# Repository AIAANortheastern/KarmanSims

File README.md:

# KarmanSims
Project Karman's simulations

Design ins

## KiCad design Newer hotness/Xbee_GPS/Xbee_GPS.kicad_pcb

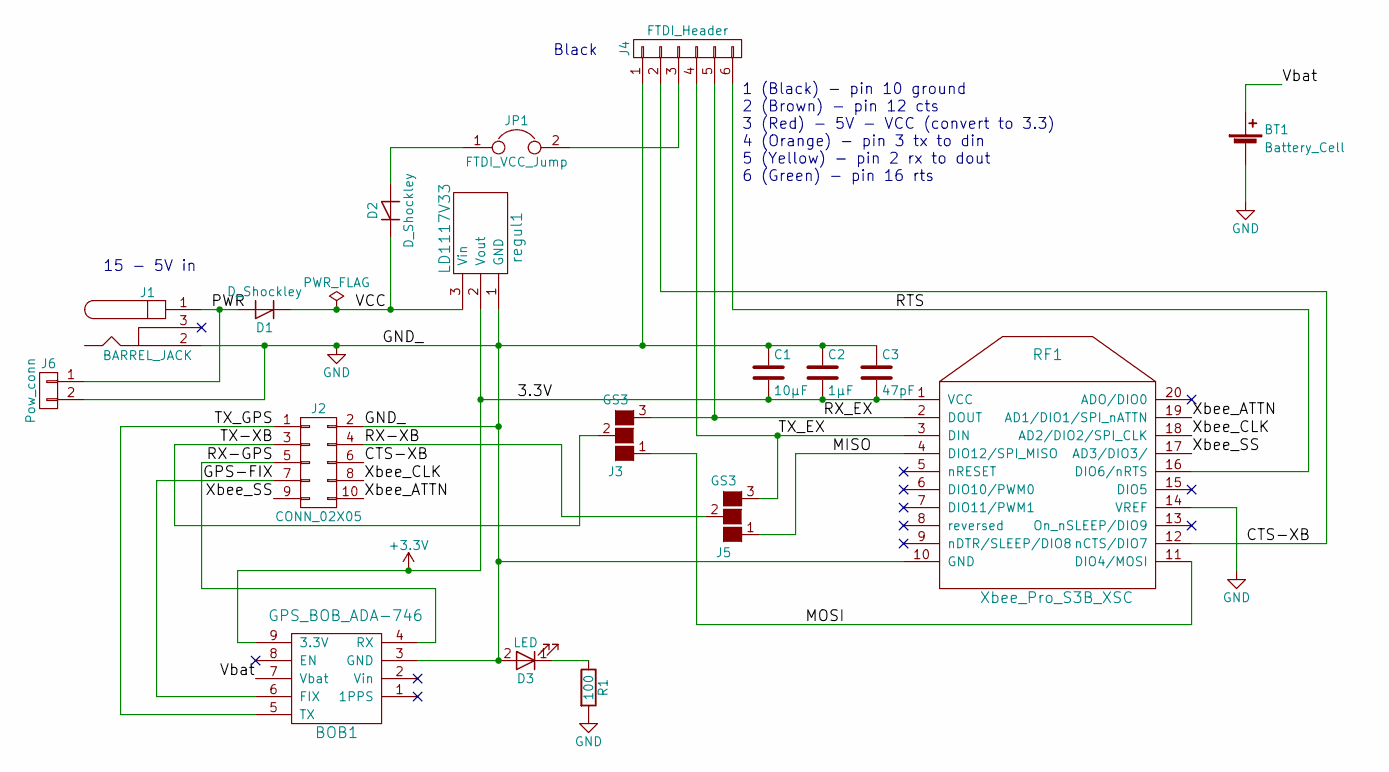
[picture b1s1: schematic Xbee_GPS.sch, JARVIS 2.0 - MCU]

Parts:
BOB1: GPS_BOB_ADA-746; GPS_BOB_A746
BT1: Battery_Cell; CR1220_Conn_TH_MPD
C1: 10µF; C_Rect_L4.6mm_W2.0mm_P2.50mm_MKS02_FKP02
C2: 1µF; C_Rect_L4.6mm_W2.0mm_P2.50mm_MKS02_FKP02
C3: 47pF; C_Rect_L4.6mm_W2.0mm_P2.50mm_MKS02_FKP02
D1, D2: D_Shockley; D_DO-35_SOD27_P7.62mm_Horizontal
D3: LED; LED-3MM
J1: BARREL_JACK; BARREL_JACK_W_Header_Holes
J2: CONN_02X05; IDC_Header_Straight_10pins
J3, J5: GS3
J4: FTDI_Header; Pin_Header_Straight_1x06_Pitch2.54mm
J6: Pow_conn; Pin_Header_Straight_1x02
JP1: FTDI_VCC_Jump; Pin_Header_Straight_1x02_Pitch2.54mm
R1: 100; R_Axial_DIN0207_L6.3mm_D2.5mm_P7.62mm_Horizontal
RF1: Xbee_Pro_S3B_XSC; Xbee_Pro_S3B
regul1: LD1117V33; TO-220_Neutral123_Vertical

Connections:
+3V3: BOB1.9 (3.3V), C1.2, C2.2, C3.2, RF1.1 (VCC), regul1.2 (Vout)
/CTS-XB: J2.6, J4.2, RF1.12 (nCTS/DIO7)
/GPS-FIX: BOB1.6 (FIX), J2.7
/MISO: J5.1 (G1), RF1.4 (DIO12/SPI_MISO)
/MOSI: J3.1 (G1), RF1.11 (DIO4/MOSI)
/PWR: D1.2 (A), J1.1, J6.1
/RTS: J4.6, RF1.16 (DIO6/nRTS)
/RX-GPS: BOB1.4 (RX), J2.5
/RX-XB: J2.4, J5.2 (G2)
/RX_EX: J3.3 (G3), J4.5, RF1.2 (DOUT)
/TX-XB: J2.3, J3.2 (G2)
/TX_EX: J4.4, J5.3 (G3), RF1.3 (DIN)
/TX_GPS: BOB1.5 (TX), J2.1
/VCC: D1.1 (K), D2.1 (K), regul1.3 (Vin)
/Vbat: BOB1.7 (Vbat), BT1.1 (+)
/Xbee_ATTN: J2.10, RF1.19 (AD1/DIO1/SPI_nATTN)
/Xbee_CLK: J2.8, RF1.18 (AD2/DIO2/SPI_CLK)
/Xbee_SS: J2.9, RF1.17 (AD3/DIO3/)
GND: BOB1.3 (GND), BT1.2 (-), C1.1, C2.1, C3.1, D3.2 (A), J1.2, J2.2, J4.1, J6.2, R1.2, RF1.10 (GND), RF1.14 (VREF), regul1.1 (GND)
unnamed: D2.2 (A), JP1.1
unnamed: D3.1 (K), R1.1
unnamed: J4.3, JP1.2

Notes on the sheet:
Black
1 (Black) - pin 10 ground 2 (Brown) - pin 12 cts 3 (Red) - 5V - VCC (convert to 3.3) 4 (Orange) - pin 3 tx to din 5 (Yellow) - pin 2 rx to dout 6 (Green) - pin 16 rts
15 - 5V in

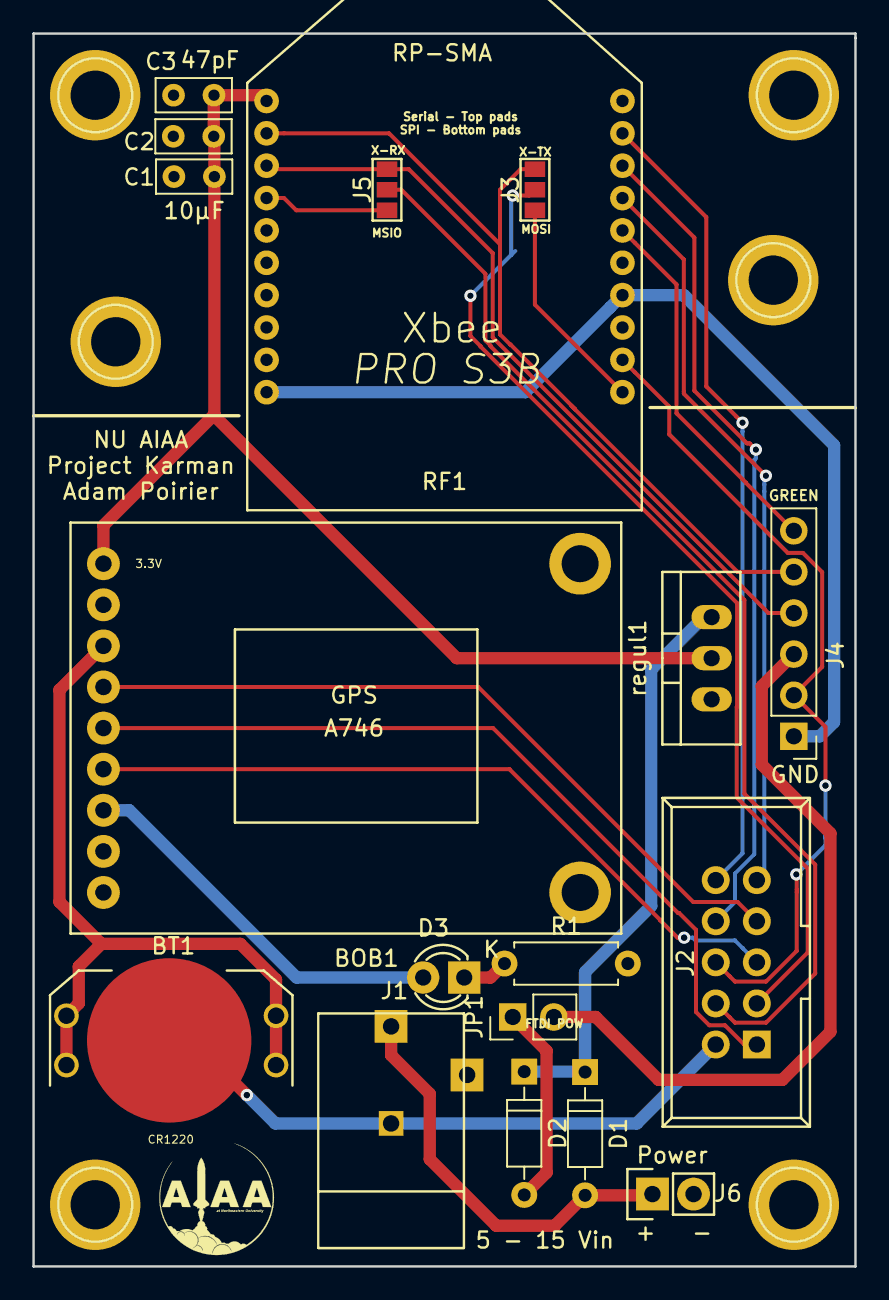
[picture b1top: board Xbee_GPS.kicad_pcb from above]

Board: 2 copper layers, 50.8 x 76.2 mm, 18 parts (0 on the bottom side), 22 nets.

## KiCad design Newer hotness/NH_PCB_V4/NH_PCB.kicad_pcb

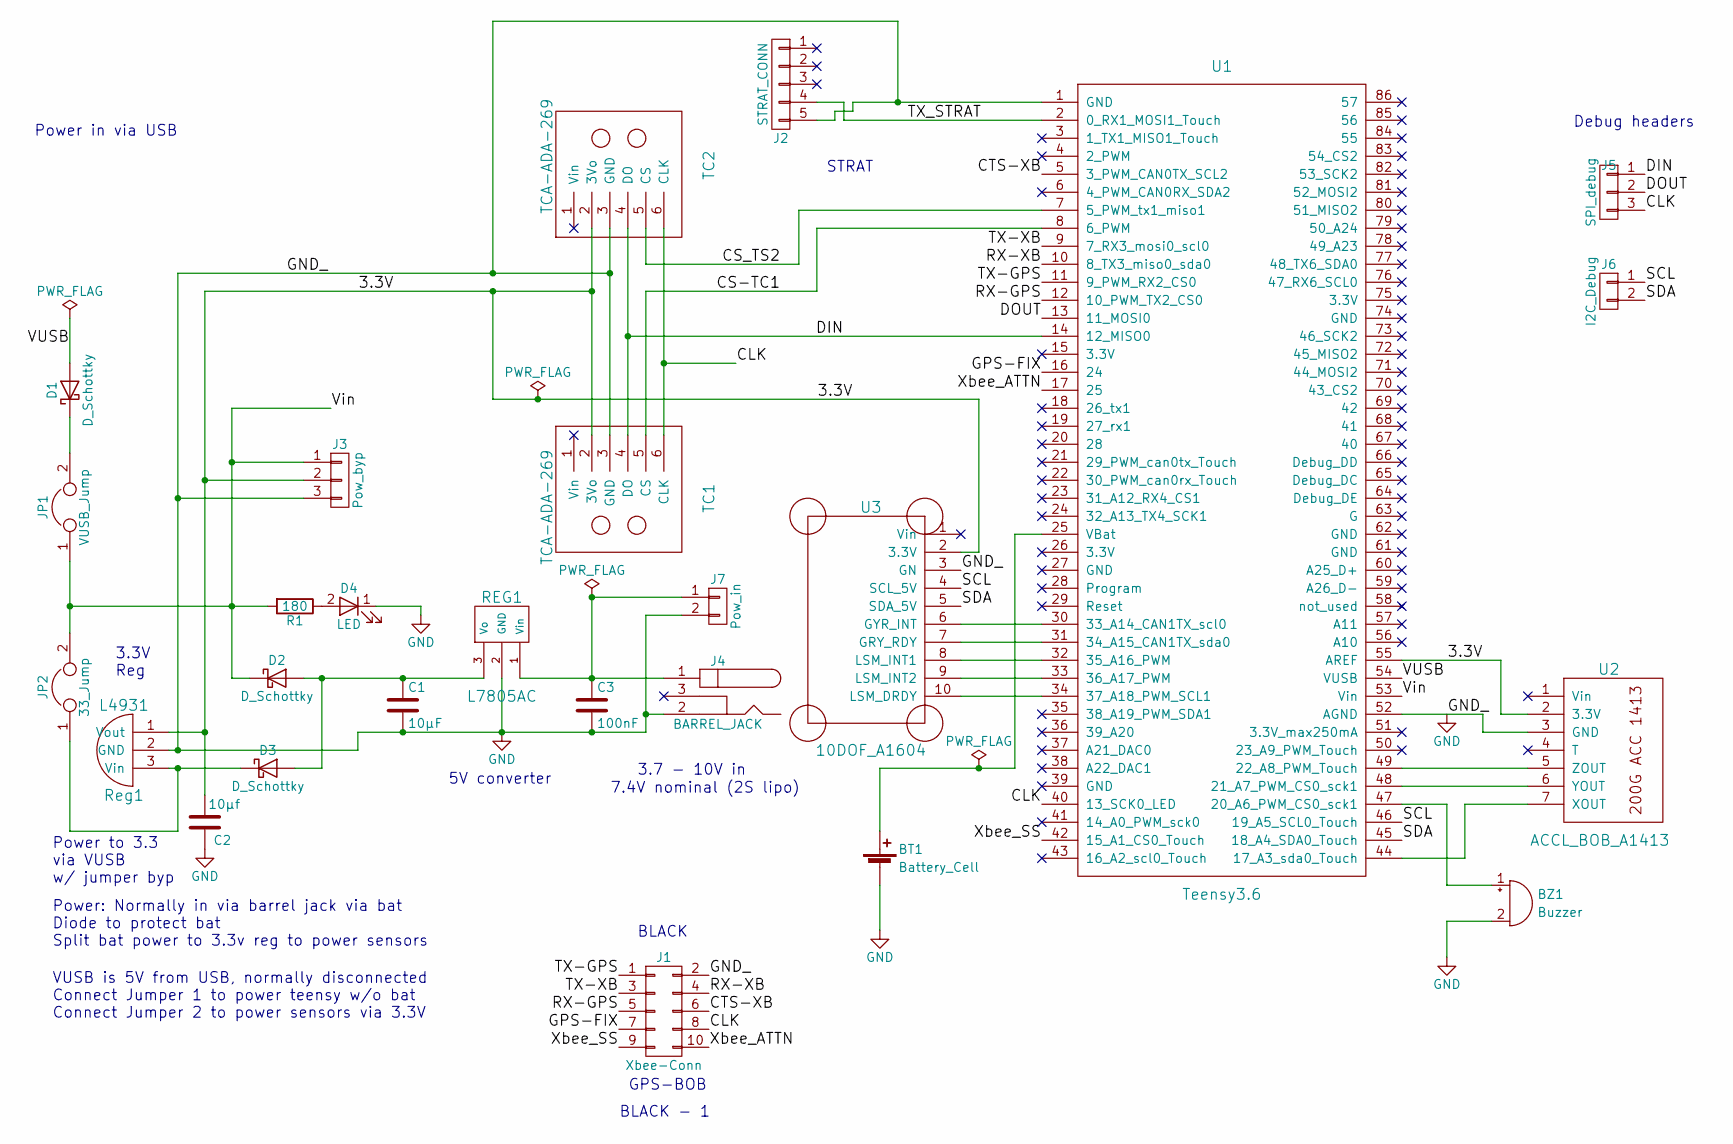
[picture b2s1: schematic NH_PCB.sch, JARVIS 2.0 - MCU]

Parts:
BT1: Battery_Cell; CR1220_Conn_TH_MPD
BZ1: Buzzer; Buzzer_A1536
C1: 10µF; C_Rect_L4.6mm_W2.0mm_P2.50mm_MKS02_FKP02
C2: 10µf; C_Rect_L4.6mm_W2.0mm_P2.50mm_MKS02_FKP02
C3: 100nF; C_Rect_L4.6mm_W2.0mm_P2.50mm_MKS02_FKP02
D1, D2, D3: D_Schottky; Diode_DO-41_SOD81_Vertical_AnodeUp
D4: LED; LED-3MM
J1: Xbee-Conn; IDC_Header_Straight_10pins
J2: STRAT_CONN; JST_SH_SM05B-SRSS-TB_05x1.00mm_Angled
J3: Pow_byp; Pin_Header_Straight_1x03
J4: BARREL_JACK; BARREL_JACK_W_Header_Holes
J5: SPI_debug; Pin_Header_Straight_1x03_Pitch2.54mm
J6: I2C_Debug; Pin_Header_Straight_1x02_Pitch2.54mm
J7: Pow_in; Pin_Header_Straight_1x02
JP1: VUSB_Jump; Pin_Header_Straight_1x02_Pitch2.54mm
JP2: 33_Jump; Pin_Header_Straight_1x02_Pitch2.54mm
R1: 180; R_Axial_DIN0207_L6.3mm_D2.5mm_P10.16mm_Horizontal
REG1: L7805AC; TO-220_Vertical
Reg1: L4931; TO-92_Inline_Wide
TC1, TC2: TCA-ADA-269; TCA_BOB_ADA269
U1: Teensy3.6; Teensy35_36
U2: ACCL_BOB_A1413; Accel_BOB_A1413
U3: 10DOF_A1604; 10DOF_BOB_ADA16014

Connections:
/3.3V: C2.2, J3.2, Reg1.1 (Vout), TC1.2 (3Vo), TC2.2 (3Vo), U1.55 (AREF), U2.2 (3.3V), U3.2 (3.3V)
/CLK: J1.8, J5.3, TC1.6 (CLK), TC2.6 (CLK), U1.40 (13_SCK0_LED)
/CS-TC1: TC1.5 (CS), U1.8 (6_PWM)
/CS_TS2: TC2.5 (CS), U1.7 (5_PWM_tx1_miso1)
/CTS-XB: J1.6, U1.5 (3_PWM_CAN0TX_SCL2)
/DIN: J5.1, TC1.4 (DO), TC2.4 (DO), U1.14 (12_MISO0)
/DOUT: J5.2, U1.13 (11_MOSI0)
/GPS-FIX: J1.7, U1.16 (24)
/RX-GPS: J1.5, U1.12 (10_PWM_TX2_CS0)
/RX-XB: J1.4, U1.10 (8_TX3_miso0_sda0)
/SCL: J6.1, U1.46 (19_A5_SCL0_Touch), U3.4 (SCL_5V)
/SDA: J6.2, U1.45 (18_A4_SDA0_Touch), U3.5 (SDA_5V)
/TX-GPS: J1.1, U1.11 (9_PWM_RX2_CS0)
/TX-XB: J1.3, U1.9 (7_RX3_mosi0_scl0)
/TX_STRAT: J2.4, U1.2 (0_RX1_MOSI1_Touch)
/VUSB: D1.2 (A), U1.54 (VUSB)
/Vin: D2.1 (K), J3.1, JP1.1, JP2.2, R1.2, U1.53 (Vin)
/Xbee_ATTN: J1.10, U1.17 (25)
/Xbee_SS: J1.9, U1.42 (15_A1_CS0_Touch)
GND: BT1.2 (-), BZ1.2 (+), C1.2, C2.1, C3.2, D4.1 (K), J1.2, J2.5, J3.3, J4.2, J7.2, REG1.2 (GND), Reg1.2 (GND), TC1.3 (GND), TC2.3 (GND), U1.1 (GND), U1.52 (AGND), U2.3 (GND), U3.3 (GN)
unnamed: BT1.1 (+), U1.25 (VBat)
unnamed: BZ1.1 (-), U1.47 (20_A6_PWM_CS0_sck1)
unnamed: C1.1, D2.2 (A), D3.2 (A), REG1.3 (Vo)
unnamed: C3.1, J4.1, J7.1, REG1.1 (Vin)
unnamed: D1.1 (K), JP1.2
unnamed: D3.1 (K), JP2.1, Reg1.3 (Vin)
unnamed: D4.2 (A), R1.1
unnamed: U1.30 (33_A14_CAN1TX_scl0), U3.6 (GYR_INT)
unnamed: U1.31 (34_A15_CAN1TX_sda0), U3.7 (GRY_RDY)
unnamed: U1.32 (35_A16_PWM), U3.8 (LSM_INT1)
unnamed: U1.33 (36_A17_PWM), U3.9 (LSM_INT2)
unnamed: U1.34 (37_A18_PWM_SCL1), U3.10 (LSM_DRDY)
unnamed: U1.44 (17_A3_sda0_Touch), U2.7 (XOUT)
unnamed: U1.48 (21_A7_PWM_CS0_sck1), U2.6 (YOUT)
unnamed: U1.49 (22_A8_PWM_Touch), U2.5 (ZOUT)

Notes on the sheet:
BLACK - 1
GPS-BOB
BLACK
STRAT
Debug headers
3.7 - 10V in
Power in via USB
7.4V nominal (2S lipo)
3.3V Reg
Power to 3.3 via VUSB w/ jumper byp
Power: Normally in via barrel jack via bat Diode to protect bat Split bat power to 3.3v reg to power sensors
VUSB is 5V from USB, normally disconnected Connect Jumper 1 to power teensy w/o bat Connect Jumper 2 to power sensors via 3.3V
5V converter

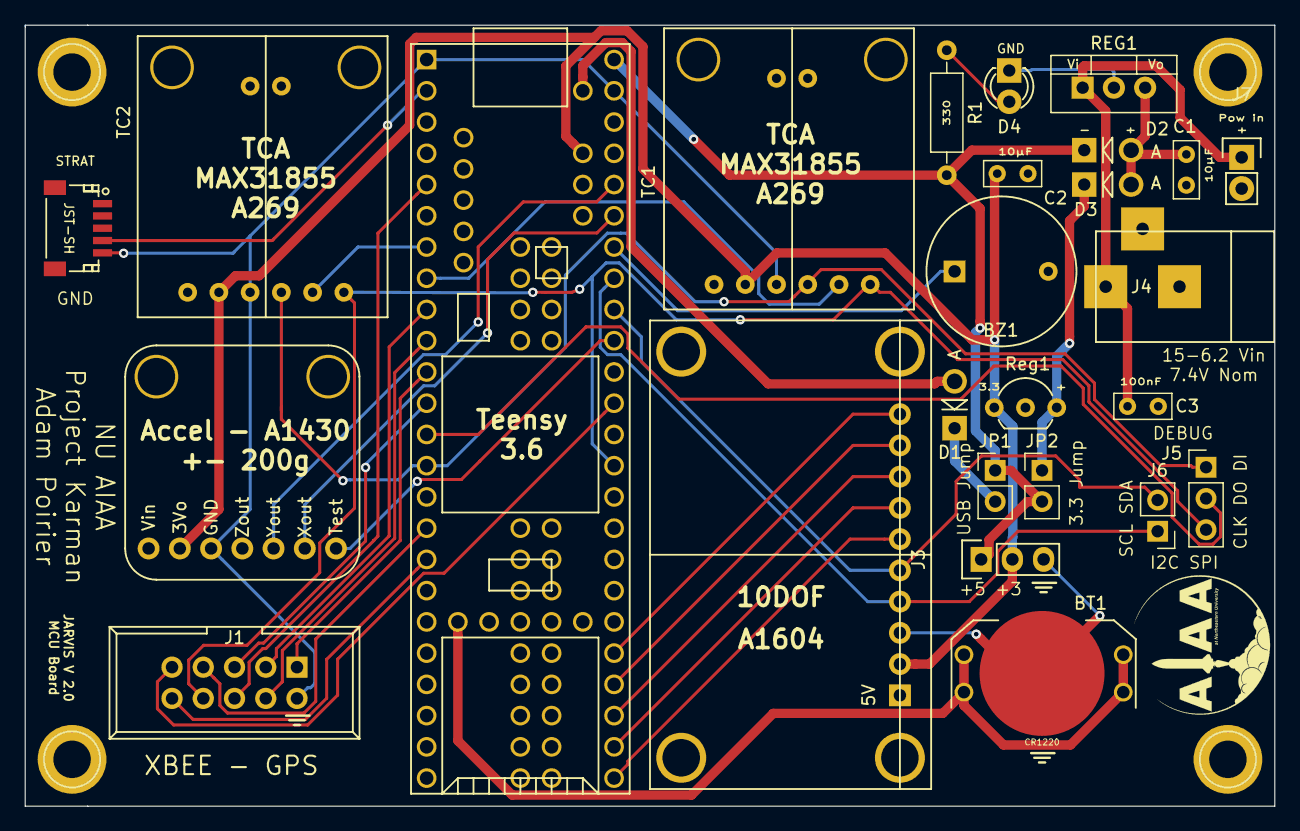
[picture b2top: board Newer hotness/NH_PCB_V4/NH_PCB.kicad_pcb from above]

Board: 2 copper layers, 101.6 x 63.5 mm, 26 parts (0 on the bottom side), 35 nets.

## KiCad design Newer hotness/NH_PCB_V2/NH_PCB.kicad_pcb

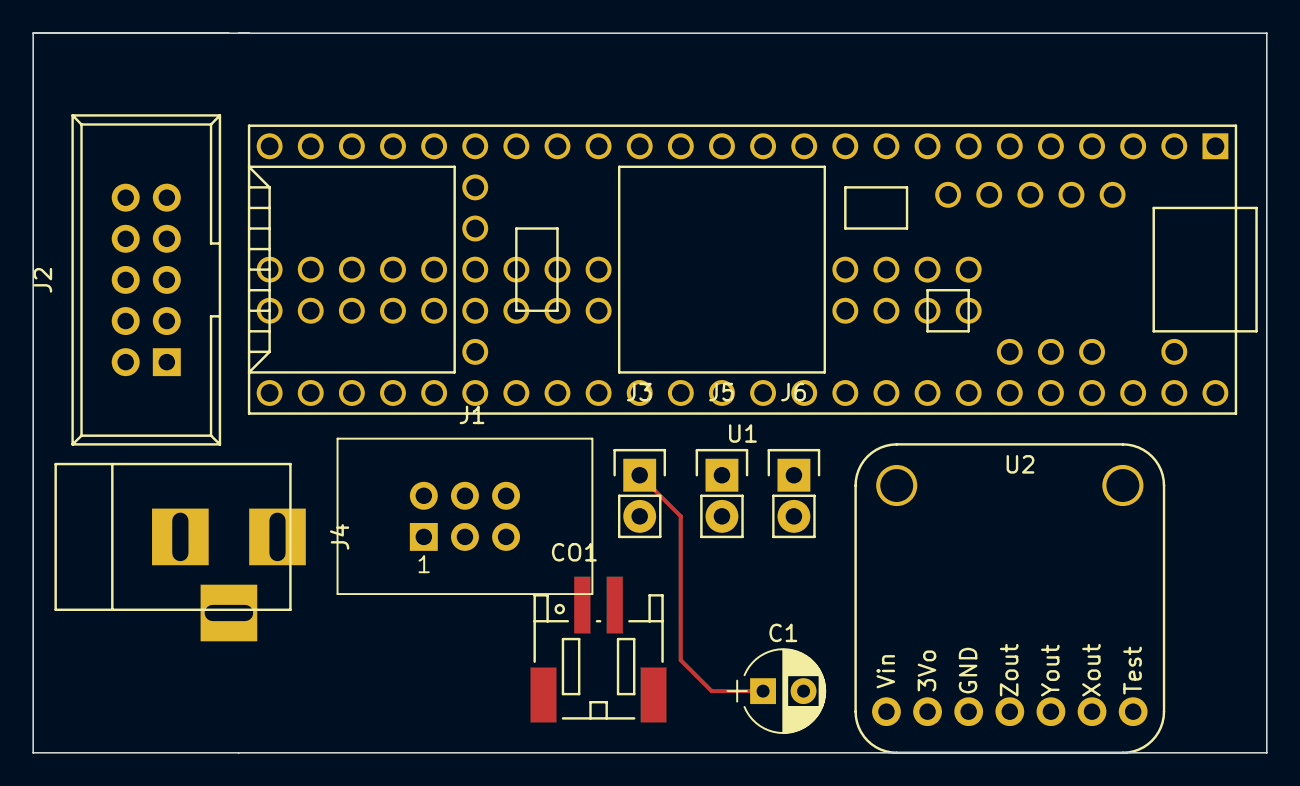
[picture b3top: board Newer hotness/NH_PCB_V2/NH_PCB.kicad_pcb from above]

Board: 2 copper layers, 76.2 x 44.4 mm, 10 parts (0 on the bottom side), 18 nets.

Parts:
C1: .1µf; CP_Radial_D5.0mm_P2.50mm
CO1: CONN_JST_2Pin; JST_PH_S2B-PH-SM4-TB_02x2.00mm_Angled
J1: CONN_02X03; IDC_Header_Straight_6pins
J2: CONN_02X05; IDC_Header_Straight_10pins
J3: POW_BYP; Pin_Header_Straight_1x02
J4: BARREL_JACK
J5, J6: CONN_01X02; Pin_Header_Straight_1x02
U1: Teensy3.5; Teensy35_36
U2: ACCL_BOB_A1413; Accel_BOB_A1413

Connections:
/5V: C1.1, J3.1, J4.1, U1.53, U1.55, U2.1
/CLK: J2.1, U1.40
/CS-TC1: J2.2, U1.8
/CTS-XB: J1.6, U1.5
/DIN: J2.3, J5.1, U1.13
/DOUT: J5.2, U1.14
/GIN: J2.7, U1.30
/GIND: J2.8, U1.31
/GND_: C1.2, J1.2, J2.4, J3.2, J4.2, U1.1, U1.52, U2.3
/RX-GPS: J1.5, U1.12
/RX-XB: J1.4, U1.10
/SCL: J2.5, J6.1, U1.46
/SDA: J2.6, J6.2, U1.45
/TX-XB: J1.3, U1.9
/XTRA: J2.10, U1.32
unnamed: U1.44, U2.7
unnamed: U1.48, U2.6
unnamed: U1.49, U2.5

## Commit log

2016-06-09 Test upload
2016-06-10 sync with drive
    added simulations in ~/Project Karman/Research/Designs/Simulations from
    Google Drive
    should really change the filenames to things that are borderline
    meaningful whatsoever
2016-06-13 Uploaded v1 RAS aero sims, along with updated open rocket files
2016-06-14 updated sims
2016-06-16 updated sims with correct mass balance
2016-06-16 I made a text file because adam said so
2016-06-21 Updated motor files
2016-06-21 added flight simulation results
2016-07-06 added legacy sims
2016-07-06 updated organisation structure
2016-07-13 updated files
2016-07-25 Updated NH sim
2016-08-15 Added parachute test rocket file
2016-08-15 Updated p-test cal
2016-10-15 Add files via upload
    Updated motor section to match the one we have
2016-10-15 Updated motor section
    Changed motor section dimensions to match the one we have
2016-10-17 Updated BTB file to properly stage
2016-10-17 added v2 of final upper stage
2016-10-18 updated to proper sizes
2016-10-19 Added actual length of upper body tube
2016-10-19 Fixing the commits
2016-10-21 Fixed location of airtight bulkhead
2016-10-22 Added the updated parachute test rocket
2016-11-09 added some files
2016-11-11 Changed motor
    Brought apogee down to about 3000 ft
2016-11-21 making sure I'm up to date
2016-12-07 Testing github on Simulations Computer
2016-12-09 Added Parachute test V4 sim
2016-12-18 making sure up to date
2016-12-18 Updated PTR V3, CAUTION: THIS FILE MAY BE OUT OF DATE BECAUSE OF PROBLEMS ON MY COMPUTER. If you know you have the most recent version, copy the file before you pull changes, then override with your 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
2017-01-02 Updated PRT sim to reflect accurate fin location. MASS OF PARACHUTE NEEDS TO BE UPDATED
2017-01-06 Updated PTR file to have 100% accurate e-bay length. NOTE: Mass of ebay is not final, and parachute and recovery harnesses are NOT massed correctly. Additionally moved fins up to comply with final de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
2017-02-17 adding PTR_V4
2017-02-18 added new full scale simulation (kevlar wraped CF)
2017-02-19 added current motor file for P
2017-02-19 added updated RASaero full scale sim
2017-02-19 Rename rasp-2:19:17.eng to rasp-2-19-17.eng
2017-02-21 Updated Parachute test to current specifications: Parachute Test V3.5.1.ork
2017-02-22 Updated BTB
2017-02-24 Updated BTB sim and added RASAero simulation
2017-02-28 updated PTR and BTB sim, along with BTB RASAero model
2017-03-01 updated BTB and PTR to use motors we are buying
2017-03-09 added standard atmospheres for reference
2017-03-12 added flight data folder with recorded PTR flight data exports
2017-03-13 updated stuff
2017-03-14 updated BTB sustainer
2017-03-14 Updated BTB RASAero
2017-03-19 updated BTB sim with 4G motor
2017-03-21 making sure sim computer is up to date
2017-03-21 removed legacy BTB sim
2017-03-30 added go-pro assembly
2017-03-30 Added the go pro assmb.
2017-04-01 updated BTB / infinity & beyond sim to work with L1115
2017-05-04 changed fin LE/TE to .5 in
2017-05-27 added motor info
2017-06-01 Added new aluminum sim
2017-07-09 Added PCB designs
2017-07-12 added final newer hotness boards
2017-07-19 PTR updates for new av-bay
2017-07-23 updated v4 pcb
2017-07-26 telemetry PCB updates
2017-07-28 updated PCB files
2017-07-31 finalized PCB layouts for the hotnesses... also for the love of god rename these rockets
2017-08-20 updated flight data
2017-08-20 Updated PTR files
    Updated PTR files
2017-08-20 updated atmos
2017-08-24 Finalized NH PCBs
2017-08-24 renamed folder for approprate _ naming
2017-10-26 updated NH
2017-10-31 added flight data from 10-28 launch
2017-10-31 added telemetry data to flight data
2017-11-08 added 2 stage BTB
2017-11-11 added 2 stage simulations
2017-11-15 newer BTB
2017-11-20 null
2017-12-08 data
2017-12-08 BlueTubeBooster V2.0 RASAero
2017-12-29 added flight data from InB
2018-02-06 updated new motor files
2018-02-07 cleaned up motor files
2018-02-07 added unity thrust tool
2018-02-09 added list functionality to motor creator
2018-02-12 updated parser tool
